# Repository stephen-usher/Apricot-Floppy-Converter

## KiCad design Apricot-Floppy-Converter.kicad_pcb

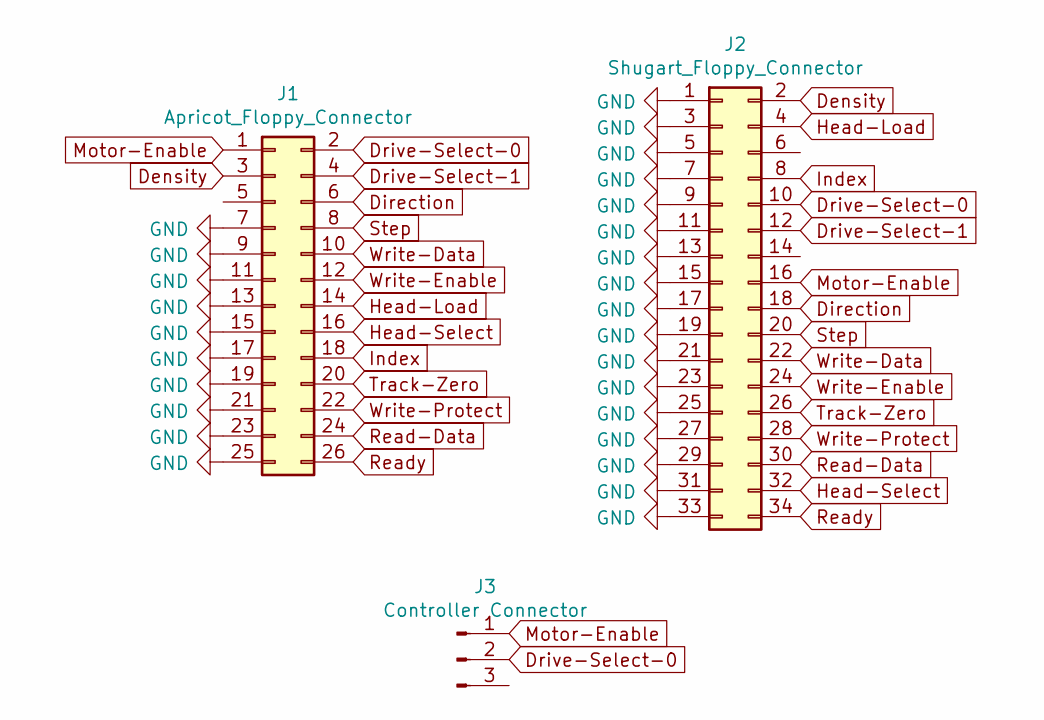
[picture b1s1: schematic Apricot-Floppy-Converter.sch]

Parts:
J1: Apricot_Floppy_Connector; PinSocket_2x13_P2.54mm_Vertical
J2: Shugart_Floppy_Connector; PinHeader_2x17_P2.54mm_Vertical
J3: Controller Connector; PinHeader_1x03_P2.54mm_Vertical

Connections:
Density: J1.3, J2.2
Direction: J1.6, J2.18
Drive-Select-0: J1.2, J2.10, J3.2
Drive-Select-1: J1.4, J2.12
GND: J1.7, J1.9, J1.11, J1.13, J1.15, J1.17, J1.19, J1.21, J1.23, J1.25, J2.1, J2.3, J2.5, J2.7, J2.9, J2.11, J2.13, J2.15, J2.17, J2.19, J2.21, J2.23, J2.25, J2.27, J2.29, J2.31, J2.33
Head-Load: J1.14, J2.4
Head-Select: J1.16, J2.32
Index: J1.18, J2.8
Motor-Enable: J1.1, J2.16, J3.1
Read-Data: J1.24, J2.30
Ready: J1.26, J2.34
Step: J1.8, J2.20
Track-Zero: J1.20, J2.26
Write-Data: J1.10, J2.22
Write-Enable: J1.12, J2.24
Write-Protect: J1.22, J2.28

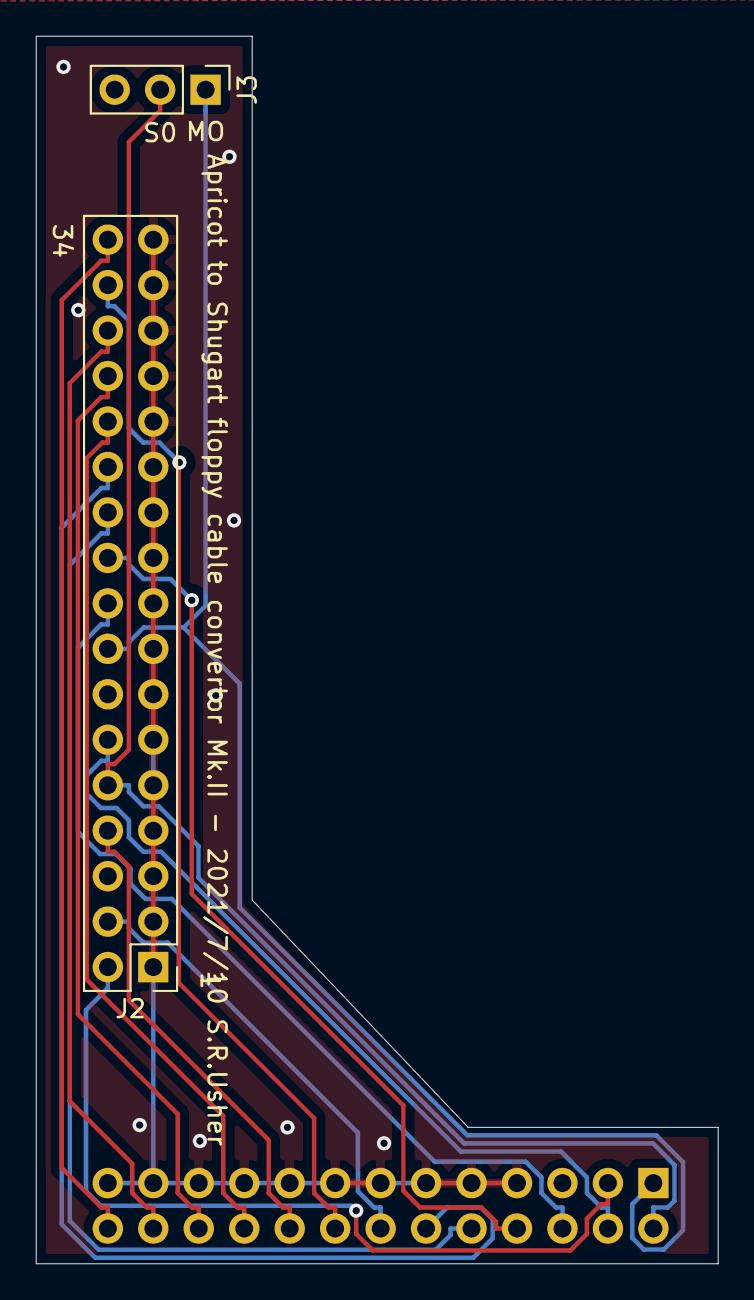
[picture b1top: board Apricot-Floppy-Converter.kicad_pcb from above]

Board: 2 copper layers, 38.1 x 68.6 mm, 3 parts (1 on the bottom side), 16 nets.
